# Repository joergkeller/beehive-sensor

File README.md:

# Beehive sensor data
Weight, temperature and humidity measurement in a beehive using Arduino and LoRaWan (TTN).\
[Deutscher Text](./README-de.md).

To support bee keepers in monitoring their bees with minimal interference, a set of sensors will measure and transmit the current state in short intervalls. Design goals:
* Energy efficiency. Devices should be able to run on batteries and solar cells for unlimited time.
* Low radiation. I do not know whether or not radio transmissions disturbe bees. Using a low-power technology like LoRa rather than GSM minimizes the effect.
* Low cost. Small microcontrollers are very affordable and sufficient for the task.

## System Overview
- **Arduino** (alternatively Uno + Dragino LoRa Shield, Dragino LoRa Mini Dev, or CubeCell LoRa Dev)\
  A small microcontroller has enough power to measure every couple of minutes. A rechargeable battery serves as buffer to measure during night and cloudy weather.\
  The device works without any human intervention except a button to put it to a 'manual mode' when working with the beehive.
    - Several (e.g. 5) DS18B20 temperature sensors using 1-wire
    - DHT11/22 temperature and humidity sensor
    - Weight cell with HX711 converter
    - LoRaWan connection (TTN)
    - Solar power and rechargeable battery (LiPo)
    - Push-Button with LED to disable temporary (manual mode)
    - Evtl. slave devices with RS-485?
    
- **LoRaWAN** TTN-Gateway/Network/Application\
  Beehives usually have no wired internet connection and high-speed connections using GSM and WLAN is avoided to keep radiation low.\
  [TheThingsNetwork](https://www.thethingsnetwork.org/) (TTN) is a global open LoRa network. If no gateway is available within some km near the beehives, an additional gateway can easily be installed. 
    - Transmits messages from the LoRa gateways to the internet, handles authorization (OTAA/ABP) and encoding/decoding of messages
    - Allows direct ThingSpeak integration (only 1 device per application with 1 channel)
    - HTTP integration allows to address any possible backend (many devices per application, see below)
    - see [TTN application](./docs/ttn-application.md)
    
- Dashboard and visualization with **ThingSpeak channel**\
  This is the quick and simple way to display the sensor data.
    - Simple to setup and share [ThingSpeak](https://thingspeak.com/)
    - Mobile app available
    - Matlab analysis possible
    - Limited to 8 fields/channel
    - No linking of multiple channels (beehives)
    - Limited user interaction (drilldown)

- **Mapping and routing** sensor data eg. using AWS (work in progress) \
  Alternative or extension to the ThingSpeak display. 
  Such a back-end application can be used to collect the sensor data and to feed a web application.
    - see [AWS serverless](./docs/aws-serverless.md)
    - Forwarding to ThingSpeak channels as above, but allowing many devices/channels per TTN application
    - Additionally storing sensor docs in DynamoDb, see [AWS recording](./docs/aws-recorder.md)
    - No restrictions of the number of fields or the way sensor data is displayed (own WebApp) 

## Device Hardware
Three boards have been tested:
- Arduino Uno + [Dragino LoRa Shield](https://www.dragino.com/products/lora/item/102-lora-shield.html)
    - Needs 5V supply
    - Many digital pins already used by shield
    - Classic Uno size and MCU (16MHz ATMega328P, 32KB FLASH, 2KB SRAM)
- [Dragino LoRa Mini Dev](https://www.dragino.com/products/lora/item/126-lora-mini-dev.html)
    - 3.3V (possible LiPo, not tested)
    - Small size, LoRa transmitter integrated
    - Classic Arduino MCU (16MHz ATMega328P, 32KB FLASH, 2KB SRAM)
- [Heltec CubeCell LoRa Dev](https://heltec.org/project/htcc-ab01/). My favorite!
    - 3.3V (possible LiPo, integrated solar charging logic)
    - Power efficient (1W solar cell with 230mAh LiPo loads on a single sunny day and has almost 2 weeks of buffer)
    - Small size, LoRa transmitter integrated
    - Stronger MCU (48 MHz ARM M0+, 128KB FLASH, 16KB SRAM)
    
Used pins:

| Pin Function | Wiring | Uno+Shield / Dragino | CubeCell |
| ------------ | ------ | ----------------- | -------- |
| 1-wire Temp sensor | pull-up resistor 4k7 to VCC | D5 | GPIO5 |
| DHT-11/22 | pull-up resistor 4k7 to VCC | D4 | GPIO4 |
| HX711 Dout | | A0 | GPIO2 |
| HX711 Sck | | A1 | GPIO3 |
| Push-Button | to GND (active low, triggers interrupt) | D3 | GPIO7 (aka battery test control) |
| LED | to VCC (active low) | A2 | GPIO1 |
       
## Transmitted LoRa message (binary encoded)
- The device measures about every 5 min
- Measures will be transmitted on significant changes or every 30 min (messages may get lost)
- Currently no uplink messages 
- Fixed size and order of measured values
- Values are transmitted as short integer values with 2 digits (-327.67 .. 327.67)
- Reserved value to represent null (-327.68) 
~~~
 "sensor": {
   "version": 0,  // command id or version
   "battery": 3.92,
   "weight": 0.37,
   "humidity": {
     "roof": 47.5
   },
   "temperature": {
     "drop": 20.68,
     "lower": 19.5,
     "middle": 19.93,
     "outer": 20.62,
     "roof": 22.2,
     "upper": 19.37
   }
 }
~~~   
   
## Checkout this project
Local installation of `git` and `Arduino IDE` assumed.\
Install the CubeCell board: https://heltec-automation-docs.readthedocs.io/en/latest/cubecell/quick_start.html
 (current version 1.3.0).
~~~
cd <project-root>
git clone https://github.com/joergkeller/beehive-sensor.git
cd beehive-sensor
git submodule init
git submodule update
~~~
To fetch the latest updates:
~~~
cd beehive-sensor
git stash
git pull
git submodule update
git stash pop
~~~

| Arduino Settings      | Value |
| ----------------------|-------|
| File > Preferences > Settings > Board Manager URLs | `https://github.com/HelTecAutomation/CubeCell-Arduino/releases/download/V1.3.0/package_CubeCell_index.json` |
| File > Preferences > Settings > Sketchbook location | `C:\...\beehive-sensor` |
| File > Open... | `C:\...\beehive-sensor\arduino_beehive_sensor_lora\arduino_beehive_sensor_lora.ino` |
| Tools > Board | `CubeCell-Board` |
| Tools > LORAWAN_REGION | `REGION_EU868` or your region |
| Tools > LORAWAN_CLASS | `CLASS_A` |
| Tools > LORAWAN_DEVEUI | `CUSTOM` |
| Tools > LORAWAN_NETMODE | `OTAA` |
| Tools > LORAWAN_ADR | `ON` |
| Tools > LORAWAN_UPLINKMODE | `UNCONFIRMED` |
| Tools > LORAWAN_NET_RESERVATION | `OFF` |
| Tools > LORAWAN_AT_SUPPORT | `OFF` |
| Tools > LORAWAN_RGB | `ACTIVE` or `DEACTIVE` |
| Monitor baud rate | `115200` |

The project already includes all required libraries (that is the reason for the submodule commands and for the local sketchbook location).

Then
1. Create free TTN account/application/device and enter OTAA/ABP authorization codes in `credentials.h`
1. Create free ThingSpeak account/channel and a TTN ThingSpeak integration with the appropriate values 
1. Compile/upload sketch
1. Activation with OTAA takes some time (even half an hour or so)
1. Press button to enter 'manual mode'
    - no LoRa messages sending, blinking LED instead
    - continous weight measuring for calibration, calculate offset/scale (eg. see [Excel sheet](./docs/Gewicht%20Eichung%20Loadcell.xlsx))
    - for temperature compensation, measure weights at different temperatures also 
    - scanning 1-wire temperature sensors one by one, note ids
    - press button again to start LoRa activation
1. Enter 1-wire sensor ids and weight calibration to `calibration.h`
1. Compile/upload sketch again 
    - Wait for OTAA activation
    - First measure should appear in the local monitor, as TTN data and in ThingSpeak channel

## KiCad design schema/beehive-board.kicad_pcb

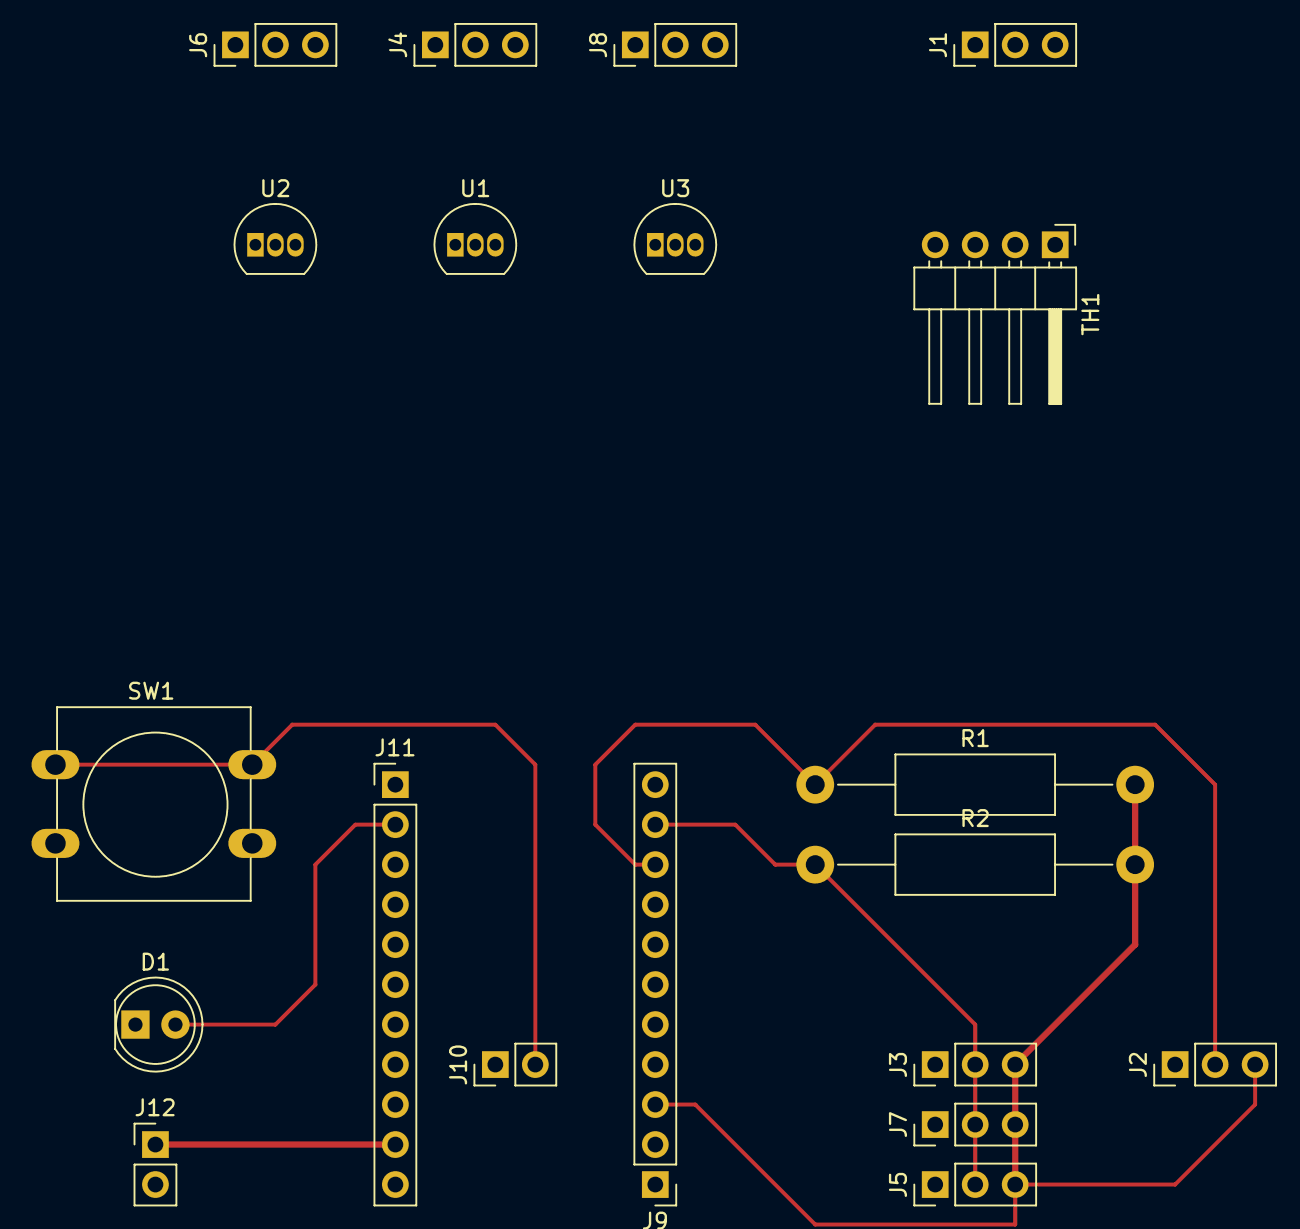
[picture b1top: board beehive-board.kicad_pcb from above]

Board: 2 copper layers, 20 parts (0 on the bottom side), 19 nets.

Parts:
D1: LED; LED_D5.0mm
J1, J4, J6, J8: Conn 1x3; PinHeader_1x03_P2.54mm_Vertical
J2, J3, J5, J7: Pin 1x3; PinHeader_1x03_P2.54mm_Vertical
J9, J11: Conn_01x11_Female; PinHeader_1x11_P2.54mm_Vertical
J10: Conn_01x02_Female; PinHeader_1x02_P2.54mm_Vertical
J12: Pin 1x2; PinHeader_1x02_P2.54mm_Vertical
R1, R2: 4k7; R_Axial_DIN0411_L9.9mm_D3.6mm_P20.32mm_Horizontal
SW1: Pushbutton; SW_PUSH-12mm
TH1: DHT22 Sensor; PinHeader_1x04_P2.54mm_Horizontal
U1, U2, U3: DS18B20; TO-92_Inline

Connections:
GND: D1.1, J2.1, J3.1, J5.1, J7.1, J9.1, J9.5, J11.11, J12.2, SW1.2
GPIO1: D1.2, J11.2
GPIO4: J3.2, J5.2, J7.2, J9.10, R2.1
GPIO5: J2.2, J9.9, R1.1
GPIO7: J10.2, SW1.1
unnamed: J1.1, TH1.4
unnamed: J1.2, TH1.2
unnamed: J1.3, TH1.1
unnamed: J4.1, U1.1
unnamed: J4.2, U1.2
unnamed: J4.3, U1.3
unnamed: J6.1, U2.1
unnamed: J6.2, U2.2
unnamed: J6.3, U2.3
unnamed: J8.1, U3.1
unnamed: J8.2, U3.2
unnamed: J8.3, U3.3
VDD: J2.3, J3.3, J5.3, J7.3, J9.3, R1.2, R2.2
VS: J11.10, J12.1

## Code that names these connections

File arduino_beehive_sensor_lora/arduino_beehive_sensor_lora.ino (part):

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 * reduce power.
 * A manual mode stops sending data but continuous to read raw data.
 * - USB/Battery voltage measurement (internal)
 * - DS18B20 temperature sensors (multiple) are read from pin D5 (GPIO5)
 * - DHT22 temperature/humidity sensor is read from pin D4 (GPIO4)
 * - Weight measured with load cell and HX711 ADC from pins A0/A1 (GPIO2/3)
 * - Push Button to switch to manual mode with pullup on pin D3 (GPIO7)
 * - LED to indicate manual mode (active low) on pin A2 (GPIO1)
 * ---
 * message version (aka command):
 *  0: sensor data v0 (short/100)
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
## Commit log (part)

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2019-08-07 untested lora adaption
2019-08-07 library as git submodule
2019-08-14 initial setup using helidon se with json-b
2019-08-21 poc using HttpIntegration and AWS ApiGateway to send data from TTN to ThingSpeak
2019-08-26 updated message format
2019-08-26 documented setup of TTN, AWS Api Gateway and ThingSpeak to handle LoRa messages. Secure communication using api-keys.
2019-08-26 updated message format documentation
2019-10-25 test & corrections with dragino shield.
2019-10-26 DS18B20 temperature sensors (multiple) are read from pin D3
2019-10-26 DHT22 temperature/humidity sensor is read from pin D4
2019-10-26 USB voltage measurement
2019-11-02 weight measured with load cell and HX711 ADC from pins A0/A1
2019-11-02 initial setup mode for load cell calibration and temperature sensor identification
2019-11-03 request LoRa confirmation, ignore undefined values, send both ThingSpeak and full sensor data in decoded structure
2019-11-03 extract sensor acquisition code to SensorReader and calibration
2019-11-03 readVcc delivers mV not 2^10 steps
2019-11-03 cleanup DraginoLoRa
2019-11-05 wait for tx-pending, print state change notifications
2019-11-09 deep sleep between measurements/transmissions
2019-11-09 refactored state handling
2019-11-10 wiring documentation for dragino shield and lora mini (no coding diffs, same pins can be used)
2019-11-11 cleanup arduino-lmic
2019-11-12 short measure interval, only send if changes above threshold (or unconditional interval)
2019-11-12 temperature sensor precision 12 bit
2019-12-27 Squashed commit of the following:
    commit a25bb9750a3cead858aee8f7a9ae6c1d97bc37ea
    Author: jokel <joerg.p.keller@gmail.com>
    Date: Fri Dec 27 19:43:18 2019 +0100
    updated CubeCell firmware
    commit 71ad22f42a743ca433fca01ed758f7569d87b290
    Author: jokel <joerg.p.keller@gmail.com>
2020-01-03 handling state entry and exit using explicit state machine
2020-01-04 fixed initialization and calling of handler
2020-01-04 state handler, allow calling instead polling
2020-01-04 state timeout with handler
2020-01-05 manual-mode state with switch and led
2020-01-05 manual-mode state reads raw data, setup state obsolete
2020-01-12 adoption to cubecell
2020-01-12 Feature/manual button (#1)
    * manual-mode state with switch and led
    * manual-mode state reads raw data, setup state obsolete
    * adoption to cubecell
2020-01-23 recording sensor data in doc-storage (dynamo-db)
2020-01-27 db queries (cli)
2020-02-02 visualize sensor data (draft)
2020-02-12 multiple days on 24h chart
2020-02-12 multi-day view for all charts, current values in titles
2020-02-19 local time, query param for device, setting and timestamp info
2020-03-08 checked board pins, separate table
2020-03-08 added wiring details (pull-up)
2020-04-07 temperature compensation of weight
2020-04-07 print name of stale state transition
2020-04-08 fixed: battery measure reuses GPIO7 as ADC_CTL and caused a user button event
2020-04-08 correct definition string used (case sensitive)
2020-04-09 fixed: battery measure reuses GPIO7 as ADC_CTL and caused a user button event (#2)
2020-04-09 Feature/red pixel in manual mode (#3)
    * allow to switch on LORAWAN_RGB neo pixel, show red pixel blinking in manual mode
    * correct definition string used (case sensitive)
2020-04-09 Feature/temperature compensation (#4)
    * temperature compensation of weight
    * print name of stale state transition
    * fixed: battery measure reuses GPIO7 as ADC_CTL and caused a user button event (#2)
    * temperature compensation of weight
    * Feature/red pixel in manual mode (#3)
    * allow to switch on LORAWAN_RGB neo pixel, show red pixel blinking in manual mode
2020-04-09 upgrade to CubeCell firmware 0.0.5
2020-04-09 updated arduino setup
2020-04-13 scripts for arduino-cli
2020-04-13 scripts for arduino-cli, workflow test action
2020-04-13 corrections for test run
2020-04-13 bugfix workflow
2020-04-13 more temperature sensors, changed message structure
2020-04-13 more temperature sensors, changed message structure with corrected decoder script
2020-04-14 refactored temperature readings, simpler to change number of 1-wire sensors
2020-04-14 upgraded dependencies to avoid vulnerability
2020-04-14 different creditials and calibrations for multiple devices in same code base
2020-04-15 device handling in lambda function
2020-04-20 additional hints for weight calibration
2020-04-22 debug output for temperature sensors
2020-04-23 updated libraries: DallasTemperature, UnifiedSensor, HX711, LowPower
2020-04-24 adopt to actual sensor ids
2020-05-03 display additional sensor data
2020-05-04 spelling correction and actual message example
2020-05-16 calibration values as real examples
2020-07-19 Bump lodash from 4.17.15 to 4.17.19 in /beehive-recorder
    Bumps [lodash](https://github.com/lodash/lodash) from 4.17.15 to 4.17.19.
    - [Release notes](https://github.com/lodash/lodash/releases)
    - [Commits](https://github.com/lodash/lodash/compare/4.17.15...4.17.19)
2020-08-31 Bump lodash from 4.17.15 to 4.17.19 in /beehive-recorder (#5)
    Bumps [lodash](https://github.com/lodash/lodash) from 4.17.15 to 4.17.19.
    - [Release notes](https://github.com/lodash/lodash/releases)
    - [Commits](https://github.com/lodash/lodash/compare/4.17.15...4.17.19)
2020-08-31 update to CubeCell 0.0.6 - renamed AdaFruit_NeoPixel - renamed ADC_CTL - fixed HX711, shiftIn not available anymore (?)
2020-08-31 undo workflow change
2020-08-31 compile-check on Arduino UNO
2020-08-31 compile-check both jobs in same description
2020-09-13 Current version CubeCell board, unix development environment
2020-09-13 check scale is ready, ask for confirmation after interval, reset if confirmation fails several times, reset after interval anyway
2020-09-13 adding witches
2020-09-13 corrected original board name
2020-09-13 optimized sketch size for Dragino boards
2020-09-13 fixed task name and cli parameter
2020-10-19 #6 enable compilation for feather32u4
2020-10-19 #6 no debug output, manual mode, one-wire thermometers, temperature correction
2020-10-19 #6 compile for feather-m0 (missing timer), bugfix device name default for CubeCell
2020-10-19 #6 bugfixing examples
2020-10-19 #6 bugfixing type in credentials-template
2021-01-05 Bump axios from 0.18.1 to 0.21.1 in /beehive-recorder
    Bumps [axios](https://github.com/axios/axios) from 0.18.1 to 0.21.1.
    - [Release notes](https://github.com/axios/axios/releases)
    - [Changelog](https://github.com/axios/axios/blob/v0.21.1/CHANGELOG.md)
    - [Commits](https://github.com/axios/axios/compare/v0.18.1...v0.21.1)
2021-01-26 Bump axios from 0.18.1 to 0.21.1 in /beehive-recorder (#8)
    Bumps [axios](https://github.com/axios/axios) from 0.18.1 to 0.21.1.
    - [Release notes](https://github.com/axios/axios/releases)
    - [Changelog](https://github.com/axios/axios/blob/v0.21.1/CHANGELOG.md)
    - [Commits](https://github.com/axios/axios/compare/v0.18.1...v0.21.1)
2021-01-26 npm update
2021-01-28 Feature/update versions (#10)
    * update setup-arduino-cli to 1.1.1
    * npm update
    * update CubeCell core to 1.2.0, change compile board settings
2021-01-28 #9 disable temperature compensation of scale if THERMOMETER_COUNT == 0
2021-01-28 merged updates
2021-01-29 replace LowPower library by Adafruit_SleepyDog that supports M0 cores
2021-01-29 reduce memory further with THERMOMETER_COUNT 0
2021-01-29 exclude all thermometer code if THERMOMETER_COUNT 0
2021-02-15 #6 read feather battery voltage
2021-02-21 no state machine timeout on CubeCell; some clean-ups
2021-03-31 Bump y18n from 4.0.0 to 4.0.1 in /beehive-recorder
    Bumps [y18n](https://github.com/yargs/y18n) from 4.0.0 to 4.0.1.
    - [Release notes](https://github.com/yargs/y18n/releases)
    - [Changelog](https://github.com/yargs/y18n/blob/master/CHANGELOG.md)
    - [Commits](https://github.com/yargs/y18n/commits)
2021-05-10 Bump lodash from 4.17.19 to 4.17.21 in /beehive-recorder
    Bumps [lodash](https://github.com/lodash/lodash) from 4.17.19 to 4.17.21.
    - [Release notes](https://github.com/lodash/lodash/releases)
    - [Commits](https://github.com/lodash/lodash/compare/4.17.19...4.17.21)
2021-05-15 Bump y18n from 4.0.0 to 4.0.1 in /beehive-recorder (#13)
    Bumps [y18n](https://github.com/yargs/y18n) from 4.0.0 to 4.0.1.
    - [Release notes](https://github.com/yargs/y18n/releases)
    - [Changelog](https://github.com/yargs/y18n/blob/master/CHANGELOG.md)
    - [Commits](https://github.com/yargs/y18n/commits)
2021-05-15 Bump lodash from 4.17.19 to 4.17.21 in /beehive-recorder (#14)
    Bumps [lodash](https://github.com/lodash/lodash) from 4.17.19 to 4.17.21.
    - [Release notes](https://github.com/lodash/lodash/releases)
    - [Commits](https://github.com/lodash/lodash/compare/4.17.19...4.17.21)
2021-05-15 only timeout if no pending message
2021-05-22 #15 aws nested stack template for storage and thingspeak forwarding
2021-07-12 initial board schema (kicad)
2021-11-13 switch the things network from v2 to v3 stack, handling both formats in transition phase
2021-11-13 Bump axios from 0.21.1 to 0.21.2 in /beehive-recorder
    Bumps [axios](https://github.com/axios/axios) from 0.21.1 to 0.21.2.
    - [Release notes](https://github.com/axios/axios/releases)
    - [Changelog](https://github.com/axios/axios/blob/master/CHANGELOG.md)
    - [Commits](https://github.com/axios/axios/compare/v0.21.1...v0.21.2)
    ---
    updated-dependencies:
2021-11-16 Bump aws-sdk from 2.656.0 to 2.1030.0 in /beehive-recorder
    Bumps [aws-sdk](https://github.com/aws/aws-sdk-js) from 2.656.0 to 2.1030.0.
    - [Release notes](https://github.com/aws/aws-sdk-js/releases)
    - [Changelog](https://github.com/aws/aws-sdk-js/blob/master/CHANGELOG.md)
    - [Commits](https://github.com/aws/aws-sdk-js/compare/v2.656.0...v2.1030.0)
    ---
    updated-dependencies:
2022-01-10 Bump axios from 0.21.1 to 0.21.2 in /beehive-recorder (#17)
    Bumps [axios](https://github.com/axios/axios) from 0.21.1 to 0.21.2.
    - [Release notes](https://github.com/axios/axios/releases)
    - [Changelog](https://github.com/axios/axios/blob/master/CHANGELOG.md)
    - [Commits](https://github.com/axios/axios/compare/v0.21.1...v0.21.2)
    ---
    updated-dependencies:
2022-01-10 Bump aws-sdk from 2.656.0 to 2.1030.0 in /beehive-recorder (#18)
    Bumps [aws-sdk](https://github.com/aws/aws-sdk-js) from 2.656.0 to 2.1030.0.
    - [Release notes](https://github.com/aws/aws-sdk-js/releases)
    - [Changelog](https://github.com/aws/aws-sdk-js/blob/master/CHANGELOG.md)
    - [Commits](https://github.com/aws/aws-sdk-js/compare/v2.656.0...v2.1030.0)
    ---
    updated-dependencies:
2022-01-10 update ansi-regex due to a vulnerability
    https://github.com/advisories/GHSA-93q8-gq69-wqmw
2022-01-10 latest npm packages
2022-01-10 upgrade cubecell core to 1.3.0
2022-01-10 changed lora include in 1.3.0
2022-01-10 Feature/cubecell130 (#19)
    * new cubecell index file on github
    * upgrade cubecell core to 1.3.0
    * changed lora include in 1.3.0
2022-01-10 npm install
2022-02-13 Bump follow-redirects from 1.14.7 to 1.14.8 in /beehive-recorder
    Bumps [follow-redirects](https://github.com/follow-redirects/follow-redirects) from 1.14.7 to 1.14.8.
    - [Release notes](https://github.com/follow-redirects/follow-redirects/releases)
    - [Commits](https://github.com/follow-redirects/follow-redirects/compare/v1.14.7...v1.14.8)
    ---
    updated-dependencies:
    - dependency-name: follow-redirects
2023-11-10 Bump axios from 0.24.0 to 1.6.0 in /beehive-recorder
    Bumps [axios](https://github.com/axios/axios) from 0.24.0 to 1.6.0.
    - [Release notes](https://github.com/axios/axios/releases)
    - [Changelog](https://github.com/axios/axios/blob/v1.x/CHANGELOG.md)
    - [Commits](https://github.com/axios/axios/compare/v0.24.0...v1.6.0)
    ---
    updated-dependencies:
